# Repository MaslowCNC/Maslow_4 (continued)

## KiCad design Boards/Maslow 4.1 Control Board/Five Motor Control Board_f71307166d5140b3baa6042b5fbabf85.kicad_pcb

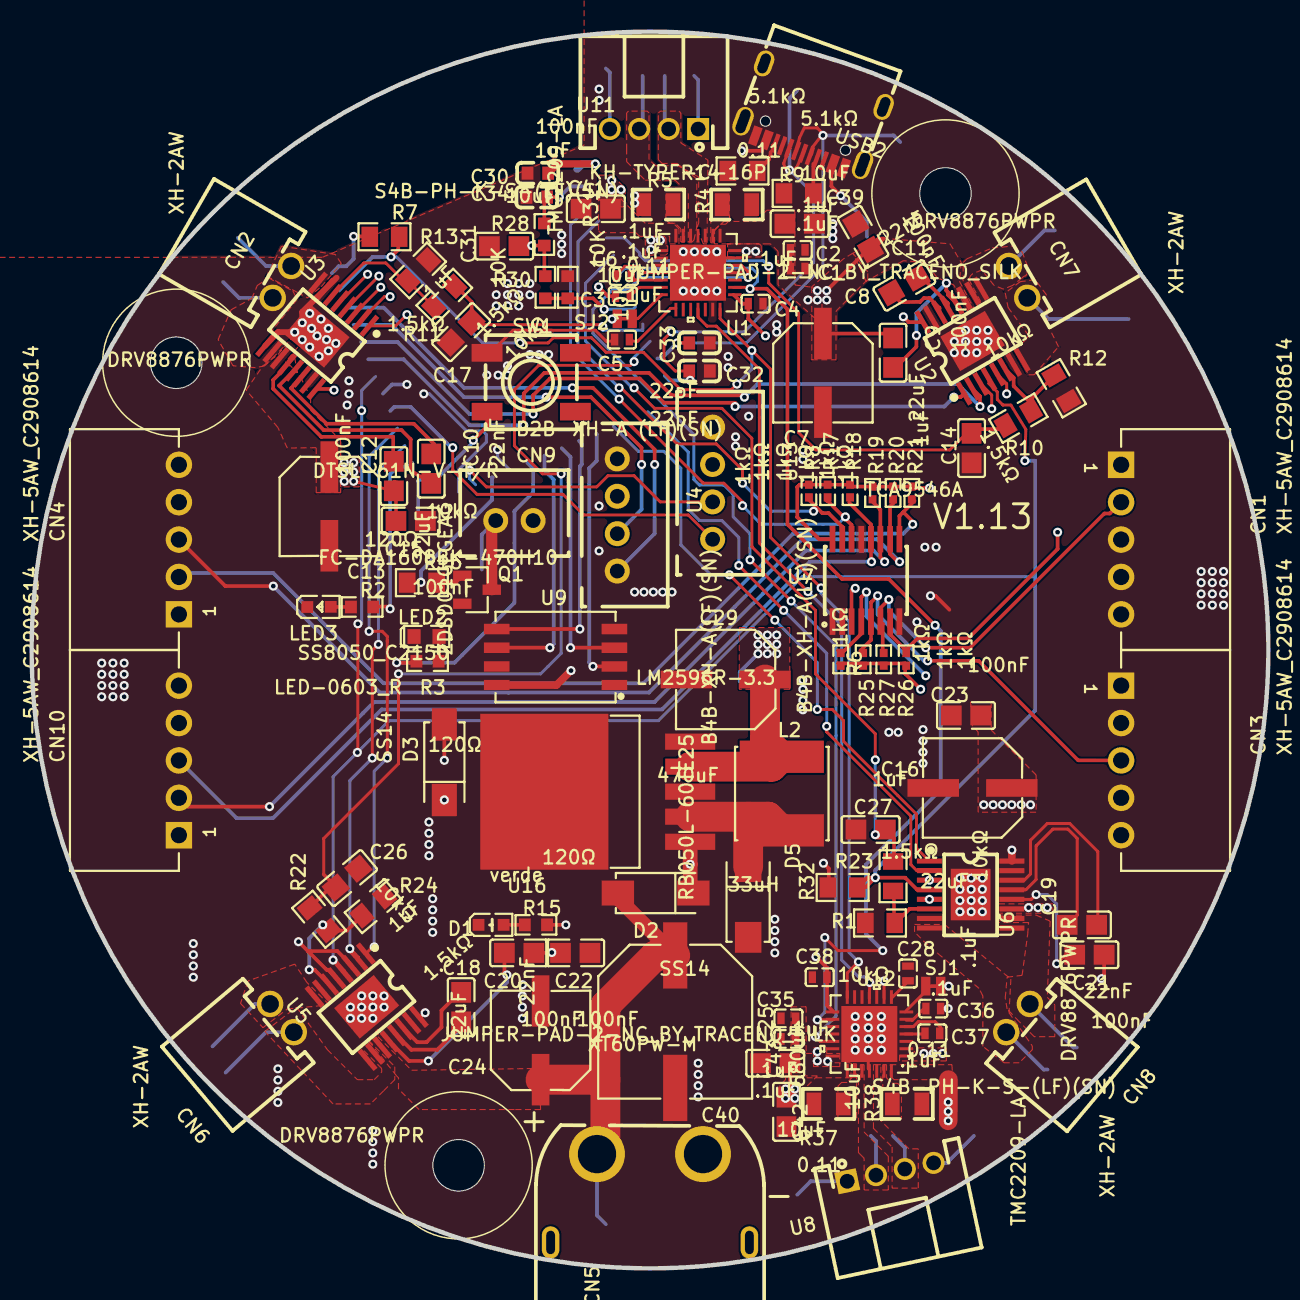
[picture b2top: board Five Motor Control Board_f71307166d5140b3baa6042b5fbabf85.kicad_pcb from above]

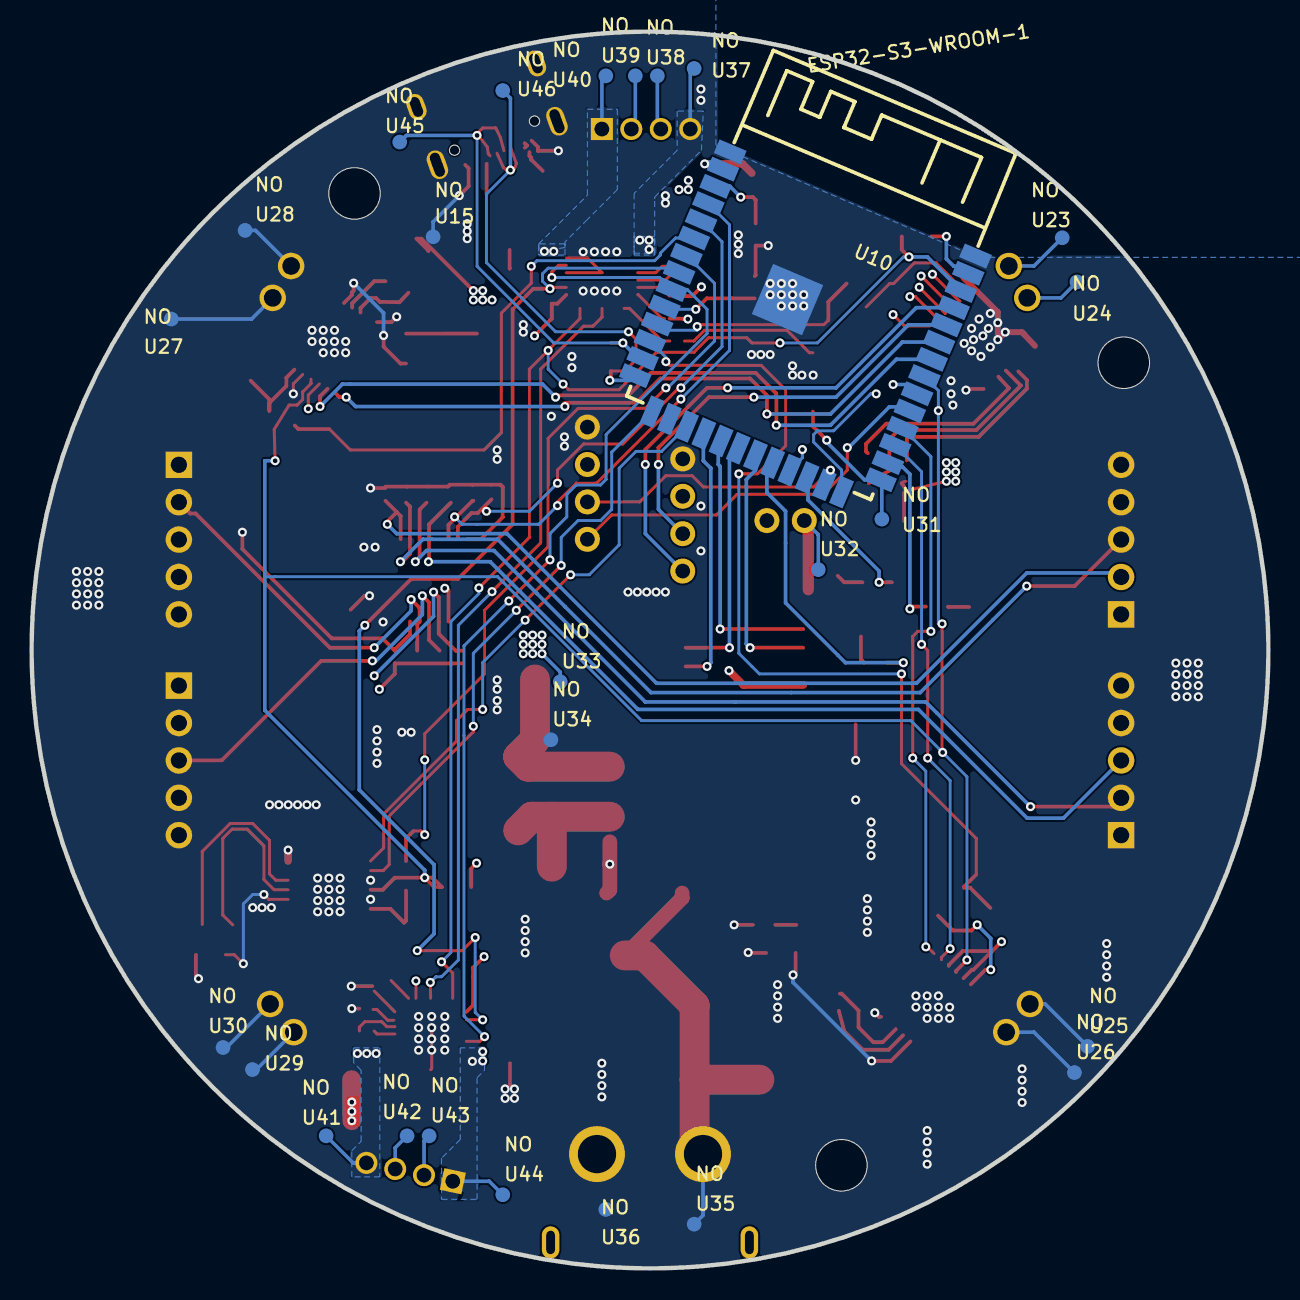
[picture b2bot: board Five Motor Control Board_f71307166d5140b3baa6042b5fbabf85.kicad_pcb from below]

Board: 4 copper layers, 84.0 x 84.0 mm, 140 parts (26 on the bottom side), 103 nets.

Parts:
C1, C2, C3, C4, C5, C6, C25, C28, C35, C36, C37, C38: .1uF; C0402
C7, C13, C16, C24: 22uF; CAP-SMD_BD6.3-L6.6-W6.6-LS7.3-FD
C8, C10, C18, C19: 22nF; C0805
C9, C11, C12, C15, C20, C21, C22, C23: 100nF; C0805
C14, C17, C26, C27: 1uF; C0805
C29: 470uF; CAP-SMD_BD6.3-L6.6-W6.6-LS7.6-RD
C30: 100nF; C0603
C31, C39, C41, C42, C43: 10uF; C0805
C32, C33: 22pF; C0603
C34: 1uF; C0603
C40: 680uF; CAP-SMD_BD10.0-L10.3-W10.3-LS10.9-FD
CN1, CN3, CN4, CN10: XH-5AW_C2908614; CONN-TH_5P-P2.54_XH-5AW_C2908614
CN2, CN6, CN7, CN8: XH-2AW; CONN-TH_2P-P2.50_XH-2AW
CN5: XT60PW-M; CONN-TH_XT60PW-M
CN9: B2B-XH-A (LF)(SN); CONN-TH_B2B-XH-A-LF-SN
D1: verde; LED0603-R-RD
D2, D3: SS14; SMA_L4.2-W2.6-LS5.3-RD
D5: RB050L-60TE25; SMA_L4.3-W2.7-LS5.1-RD
Hole_gge29897: Hole_gge29897
Hole_gge29907: Hole_gge29907
Hole_gge29912: Hole_gge29912
L2: 33uH; IND-SMD_L6.0-W6.0
LED2: LED-0603_R; LED0603_RED
LED3: FC-DA1608BK-470H10; LED0603-RD
Q1: SS8050_C2150; SOT-23-3_L2.9-W1.3-P1.90-LS2.4-BR
R1, R7, R12, R13, R24: 1.5kΩ; R0805
R2, R3, R15: 120Ω; R0603
R4, R5, R37, R38: 0.11; R0805
R6, R8, R17, R18, R19, R20, R21, R25, R26, R27: 1kΩ; R0402
R9, R14: 5.1kΩ; R0805
R10, R11, R16, R22, R23, R32: 10kΩ; R0805
R28, R30, R31: 10K; R0603
SJ1, SJ2: JUMPER-PAD-2-NC_BY_TRACENO_SILK; PAD-JUMPER-2-NC_BY_TRACE_NO_SILK
SW1: DTSL-61N-V-T/R; SW-SMD_4P-L6.2-W6.4-P4.00-LS7.2
U1, U12: TMC2209-LA
U2, U3, U5, U6: DRV8876PWPR; HTSSOP-16_L5.0-W4.4-P0.65-LS6.4-BL-EP
U4, U13: B4B-XH-A(LF)(SN); CONN-TH_B4B-XH-A-LF-SN
U7: TCA9546A; SOP-16_L5.0-W4.4-P0.65-LS6.4-BL
U8, U11: S4B-PH-K-S-(LF)(SN); CONN-TH_4P-P2.00_S4B-PH-K-S-LF-SN
U9: ZDSD01GLGEAG; LGA-8_L6.0-W8.0-P1.27-BL
U10: ESP32-S3-WROOM-1
U15, U23, U24, U25, U26, U27, U28, U29, U30, U31, U32, U33, U34, U35, U36, U37, U38, U39, U40, U41, U42, U43, U44, U45, U46: NO; 1-POINT_TEST-POINT
U16: LM2596R-3.3; TO-263-5_L10.2-W8.6-P1.70-LS14.4-TL
USB2: KH-TYPE-C-16P; USB-C-SMD_KH-TYPE-C-16P

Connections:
3V3: C4.1, C29.1, C30.2, C31.2, C38.1, CN1.1, CN3.1, CN4.1, CN10.1, L2.2, R6.2, R8.2, R15.2, R17.2, R18.2, R19.2, R20.2, R21.2, R25.2, R26.1, R27.2, R28.2, R30.2, R32.2, SJ1.1, SJ2.1, U1.15, U2.3, U2.5, U2.16, U3.3, U3.5, U3.16, U4.2, U5.3, U5.5, U5.16, U6.3, U6.5, U6.16, U7.3, U7.16, U9.8, U10.2, U12.9, U12.15, U13.2, U16.4, U33.1
A1+: U8.2, U12.24, U43.1
A1-: U8.1, U12.21, U44.1
A2+: U1.24, U11.2, U39.1
A2-: U1.21, U11.1, U40.1
ADCBL: C26.2, R22.1, U10.12
ADCBR: C27.2, R23.1, U10.7
ADCTL: C17.2, R11.1, U10.11
ADCTR: C14.2, R10.1, U10.6
AUX1: U10.25, U13.3
AUX2: U10.31, U13.4
AXISHEALTHLED: R3.2, U10.22
B1+: U8.3, U12.26, U42.1
B1-: U8.4, U12.1, U41.1
B2+: U1.26, U11.3, U38.1
B2-: U1.1, U11.4, U37.1
BLIN1: U5.1, U10.30
BLIN2: U5.2, U10.29
BLOUT1: CN6.2, U5.8, U25.1
BLOUT2: CN6.1, U5.10, U26.1
BOARDVERSION: R30.1, R31.2, U10.10
BOOT: SW1.2, U10.27, U31.1
BRIN1: U6.1, U10.17
BRIN2: U6.2, U10.15
BROUT1: CN8.2, U6.8, U29.1
BROUT2: CN8.1, U6.10, U30.1
C3_2: C3.2, U1.6
CLKV: U9.3, U10.20
COOLINGFAN: R16.1, U10.24
D1_1: D1.1, R15.1
DIAG: U1.11, U12.11
FAULT: R32.1, U2.4, U3.4, U5.4, U6.4, U10.33
GND: C1.2, C2.2, C4.2, C5.1, C7.2, C11.1, C13.2, C14.1, C15.1, C16.2, C17.1, C22.1, C23.1, C24.2, C25.2, C26.1, C27.1, C28.1, C29.2, C30.1, C31.1, C32.1, C33.1, C34.1, C35.2, C38.2, C39.2, C40.2, C41.2, C42.2, C43.2, CN1.4, CN1.5, CN3.4, CN3.5, CN4.4, CN4.5, CN5.1, CN10.4, CN10.5, D1.2, D5.2, LED2.2, LED3.1, Q1.2, R1.1, R4.2, R5.2, R9.1, R12.1, R13.1, R14.1, R24.1, R31.1, R37.2, R38.2, SW1.4, U1.2, U1.3, U1.13, U1.18, U1.20, U1.25, U1.29, U2.7, U2.9, U2.15, U2.17, U3.7, U3.9, U3.15, U3.17, U4.1, U5.7, U5.9, U5.15, U5.17, U6.7, U6.9, U6.15, U6.17, U7.1, U7.2, U7.8, U7.13, U9.4, U10.1, U10.40, U10.41, U12.2, U12.3, U12.13, U12.18, U12.20, U12.25, U12.29, U13.1, U16.3, U16.5, U34.1, U36.1, USB2.1, USB2.2, USB2.3, USB2.4, USB2.A1, USB2.A12, USB2.B1, USB2.B12
L2_1: D5.1, L2.1, U16.2
LED2_1: LED2.1, R3.1
LED3_2: LED3.2, R2.1
MCU_RST: C34.2, R28.1, U10.3
MISOV: U9.6, U10.21
MOSIV: U9.5, U10.19
MZDIRECTION: U1.19, U10.9, U12.19
MZSTEP: U1.16, U10.8, U12.16
Q1_1: Q1.1, R16.2
Q1_3: CN9.2, Q1.3, U32.1
R4_1: R4.1, U1.23
R5_1: R5.1, U1.27
SCL: R17.1, U7.14, U10.4
SCL0: CN3.3, R25.1, U7.5
SCL1: CN1.3, R26.2, U7.7
SCL2: CN4.3, R20.1, U7.10
SCL3: CN10.3, R18.1, U7.12
SDA: R8.1, U7.15, U10.5
SDA0: CN3.2, R6.1, U7.4
SDA1: CN1.2, R27.1, U7.6
SDA2: CN4.2, R21.1, U7.9
SDA3: CN10.2, R19.1, U7.11
SD_CS: U9.2, U10.18
SERIALRX: U4.3, U10.36
SERIALTX: U4.4, U10.37
TLIN1: U3.1, U10.26
TLIN2: U3.2, U10.23
TLOUT1: CN2.2, U3.8, U23.1
TLOUT2: CN2.1, U3.10, U24.1
TRIN1: U2.1, U10.35
TRIN2: U2.2, U10.34
TRINAMICRX: R7.1, U1.14, U10.38, U12.14
TRINAMICTX: R7.2, U10.39
TROUT1: CN7.2, U2.8, U27.1
TROUT2: CN7.1, U2.10, U28.1
U1_4: C6.1, U1.4
U1_5: C6.2, U1.5
U1_7: SJ2.2, U1.7
U1_8: C5.2, U1.8
U2_6: R10.2, R12.2, U2.6
U2_12: C9.2, U2.12
U2_13: C8.2, U2.13
U2_14: C8.1, U2.14
U3_6: R11.2, R13.2, U3.6
U3_12: C12.2, U3.12
U3_13: C10.2, U3.13
U3_14: C10.1, U3.14
U5_6: R22.2, R24.2, U5.6
U5_12: C20.2, U5.12
U5_13: C18.2, U5.13
U5_14: C18.1, U5.14
U6_6: R1.2, R23.2, U6.6
U6_12: C21.2, U6.12
U6_13: C19.2, U6.13
U6_14: C19.1, U6.14
U12_4: C37.1, U12.4
U12_5: C37.2, U12.5
U12_6: C36.2, U12.6
U12_7: SJ1.2, U12.7
U12_8: C28.2, U12.8
U12_23: R37.1, U12.23
U12_27: R38.1, U12.27
U16_1: D2.1, D3.1, U16.1
USB2_A5: R9.2, USB2.A5
USB2_B5: R14.2, USB2.B5
USB5V: D3.2, U15.1, USB2.A4, USB2.A9, USB2.B4, USB2.B9
USBD+: C32.2, U10.14, U46.1, USB2.A6, USB2.B6
USBD-: C33.2, U10.13, U45.1, USB2.A7, USB2.B7
VCC: C1.1, C2.1, C3.1, C7.1, C9.1, C11.2, C12.1, C13.1, C15.2, C16.1, C20.1, C21.1, C22.2, C23.2, C24.1, C25.1, C35.1, C36.1, C39.1, C40.1, C41.1, C42.1, C43.1, CN5.2, CN9.1, D2.2, U1.22, U1.28, U2.11, U3.11, U5.11, U6.11, U12.22, U12.28, U35.1
WIFILED: R2.2, U10.28

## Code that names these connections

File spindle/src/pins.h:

#pragma once

// ------------------- Pin Map -------------------

// Motor Driver U14 (MP6541A) - HSx/LSx inputs, active high
#define INHA 18
#define INLA 9
#define INHB 8
#define INLB 10
#define INHC 3
#define INLC 14

// Motor Driver U15 (MP6541A)
#define INHA2 21
#define INLA2 4
#define INHB2 47
#define INLB2 35
#define INHC2 48
#define INLC2 36

// Current Sense ADC - Motor 1 (U14)
#define CURA 5
#define CURB 6
#define CURC 7

// Current Sense ADC - Motor 2 (U15)
#define CURA2 15
#define CURB2 16
#define CURC2 17

// Driver fault / sleep control.  The MP6541A has no SPI: nFAULT is an open-drain output
// (5.1k pull-up on the board) and nSLEEP - shared by BOTH drivers - is the only way to power
// the gate drivers down.  nSLEEP has an internal pull-down, so the drivers sleep out of reset.
#define DRV_NFAULT1 11    // U14 nFAULT
#define DRV_NFAULT2 12    // U15 nFAULT
#define DRV_NSLEEP  13    // U14 + U15 nSLEEP (shared)

// Vacuum / board cooling fan
#define FAN_PWM_PIN 40

// Inter-board link UART (to FluidNC XY board)
// Spindle GPIO39 (RX) <-> XY GPIO15 (TX)
// Spindle GPIO38 (TX) <-> XY GPIO16 (RX)
#define LINK_RX_PIN 39
#define LINK_TX_PIN 38

// Z-axis homing beam break (top-of-travel detector)
// IR LED emitter driven by GPIO1 (through 100R), phototransistor collector read on GPIO2
// (10k pull-up to 3V3, emitter to GND): the pin reads LOW when the beam reaches the
// detector and HIGH when the beam is interrupted.
#define BEAM_LED_PIN      1
#define BEAM_DETECT_PIN   2
